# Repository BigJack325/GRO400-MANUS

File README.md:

# GRO400-MANUS
4th Semester Upgraded Hexapod Project for Robotique Engineering Sherbrooke University

<div id="ManUS" align="center">
    <h1>ManUS</h1>
    <h3>Hexapod Robot : Upgraded Version | Promo66-UdeS-GRO</h3>
</div>
<div id="badges" align="center">

</div>

**This academic project is based on an older academic project from robotic engineering undergraduates at Université de Sherbrooke. "Manu" is an hexapod robot able to interact with his environments. Along with 6 legs comes a camera mounted on a 3D printed head, elevating Manu to a whole new level of robotic hexapod. It can walk, look around and chase targets all around him in a restrained area/arena.**

## Table of Contents
- [Setup](#Setup)
    - [Setup for Users](#SetupUsers)
- [Documentation](#Documentation)
    - [Servos Classification](#Servosclassification)
    - [Assembly Guide](#assemblyguide)
    - [Electrical Schematic](#electricalschematic)
    - [Electrical Diagram of the Shield](#electrical)
    - [Code Overview](#Codeexplication)
- [Robot Operation](#Operation)
    - [Robot Movement](#Movement)
    - [Robot Vision](#Vision)
    - [HMI And Robot Controls](#Controls)
- [External Resources](#Ressources)
    - [Battery, Power Source, and Charger](#Battery)
    - [Microcontroller Board](#Controller)
    - [On-Board Computer](#Computer)
    - [Servomotor for the legs](#Servo1)
    - [Servomotor for the mandibles](#Servo2)
    - [Current Sensor](#Current)
    - [DC/DC Converter](#DCDC)
    - [Fuse 10 Amp](#Fuse)

## Setup

#### Setup for Users

<b>Step 1.</b> Connect Raspberry Pi camera to the Raspberry Pi before booting it up;
<br/>
<b>Step 2.</b> Clone this repository: https://github.com/EDP325/GRO400-MANUS.git
<br/>
<b>Step 3.</b> Create a new virtual environment, install dependencies, and add virtual environment to the Python Kernel by running in terminal:
<pre>
cd ./Hexapod-Master/Hexapod_Qt
./install_venv_pi.sh
</pre> 
<b>Step 4.</b> Connect the hexapod's microcontroller (Arduino) to Raspberry Pi;
<br/>
<b>Step 5.</b> Open the file <b>main.cpp</b> in the <b>./Hexapod-Master/Hexapod_Arduino/src</b> folder, and build the code into the microcontroller with your favorite IDE with PlatformIO;
<br/>
<b>Step 6.</b> Upload the <b>main.cpp</b> in the Arduino;
<br/>
<b>Step 7.</b> Run the file <b>MANUS_QT</b> in the <b>./Hexapod-Master/Hexapod_Qt</b> folder;
<br/>
<b>Step 8.</b> Initialize the serial communication.

## Documentation
#### <a id = "Servosclassification">Classification of the robot servos:</a>

#### <a id= "assemblyguide">Assembly Guide</a>
You need to 3D print the necessary parts that you can find in the *./CAD* folder.   
We have a complete assembly guide [here](https://github.com/EDP325/GRO400-MANUS/wiki):

#### <a id = "electricalschematic"> Electrical Schematic</a>

#### <a id= "electrical">Electrical Diagram of the Shield: </a>

#### <a id="Codeexplication">Code Overview</a>

The code is divided in two main sections. The first one is all about the robot's movment and is written in C++ and is run on the Arduino.  This code uses switch cases depending one the manuel/automatic mode and which movment to do.
The second section  includes the vision algorithm and the HMI.  It is written in Python and is run on the Raspberry Pi.  It is made to detect the chosen images and display  the HMI, a screen connected to the Pi.  We chose to use VNCviewer to connect to the Raspberry Pi through Wifi to have a remote connection to the hexapod.

## Robot Operation

#### Robot Movement
The robot can move forward, backward and sideways.  It can also rotate clockwise and counterclockwise.  The head can rotate and the mandibles can open cand close.  

#### Robot Vision
The robot has a vision algorithm that detects these two images: 

#### HMI And Robot Controls
Our HMI shows:
- The current view of the cam with TensorFlow AI detection;
- The angles of all the servos;
- A map of the arena with the position of the hexapod;
- Informations for the camera and messages from the Arduino
- Information about battery voltage percentage
- A graphic that shows the the value of a variable over time
- A ComboBox to see every connected ports to initialize serial communication
- Buttons to move the robots

## External ressources

Under this section, you will find external links and descriptions of the project's external resources.

#### Battery

- Brand Name: Makita
- Model:
    - Battery: BL1041B
    - Power Source: PE00000028
    - Charger: DC10SB
- ASIN:
    - Battery: B017GQJDVM
    - Charger: B01FY4XCB0
- Information / Resources:
    - [Makita Battery Webpage](https://www.makitatools.com/products/details/BL1041B)
    - [Makita Power Source Webpage](https://www.makitatools.com/products/details/PE00000028)
    - [Makita Charger Webpage](https://www.makitatools.com/products/details/DC10SB)

#### Microcontroller board

- Brand Name: Arduino
- Model: Mega 2560 R3 (A000067)
- ASIN: B0046AMGW0
- Information / Resources: [Arduino Webpage](https://store.arduino.cc/mega-2560-r3)

#### Onboard computer

- Brand Name: Raspberry Pi
- Model: 3B
- ASIN: B01LPLPBS8
- Information / Resources: [Raspberry Pi Webpage](https://www.raspberrypi.org/products/raspberry-pi-3-model-b/)

#### Servomotor for the legs

- Brand Name : VIPMOON
- Model : MG996R
- Information / Resources : [Amazon Webpage](https://www.amazon.ca/-/fr/gp/product/B07VT5T9JC/ref=ewc_pr_img_1?smid=A2FI4MJY3VQVX5&psc=1)

#### Servomotor for the mandibles

- Model : MG90S
- Information / Resources : [Amazon Webpage](https://www.amazon.ca/servomoteur-h%C3%A9licopt%C3%A8re-m%C3%A9tallique-intelligent-commandes/dp/B08W26FNQD/)
#### Current sensor

- Brand Name : ROBOJAX
- Model : ACS712
- ASIN :B07YP4693C
- Information / Resources : [Amazon Webpage](https://www.amazon.ca/gp/product/B07YP4693C/ref=ppx_yo_dt_b_asin_title_o02_s00?ie=UTF8&psc=1)

#### DC/DC Converter

- Brand Name : Tyenaza
- Model : Tyenazad03xwg94zo
- ASIN :
- Information / Resources : [Amazon Webpage](https://www.amazon.ca/gp/product/B097QT54C7/ref=ppx_yo_dt_b_asin_title_o02_s00?ie=UTF8&amp&psc=1)

#### Pi Camera

- Brand Name : Keyestudio
- Model : 8541582798
- ASIN :
- Information / Resources : [Amazon Webpage](https://www.amazon.ca/gp/product/B073RCXGQS/ref=ppx_yo_dt_b_asin_title_o01_s00?ie=UTF8&psc=1)
    
fuse 10 AMP
#### <a id="Fuse">Fuse 10 AMP 250V</a>

- Brand Name : Littelfuse
- Model : Littelfuse 5x15MM. FAST ACTING 10A.250V.
- Information / Resources :You can buy fuse at any electronics store near your house.  We bought ours [here](https://electro5.com/fr/product/231621/littlefuse-5x15mm-fast-acting-10a250v/)

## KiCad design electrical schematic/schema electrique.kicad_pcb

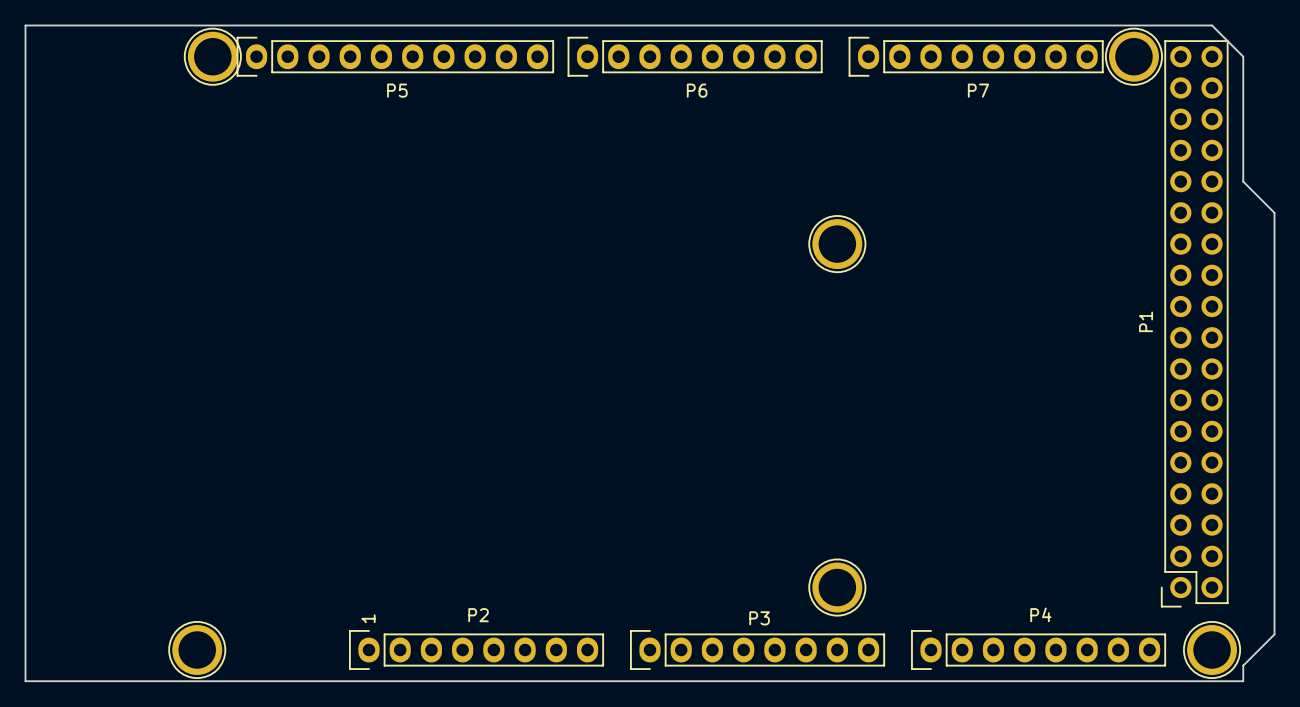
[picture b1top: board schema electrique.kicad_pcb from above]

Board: 2 copper layers, 101.6 x 53.3 mm, 13 parts (0 on the bottom side), 2 nets, no tracks yet.

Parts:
P1: Digital; Socket_Strip_Arduino_2x18
P2: Power; Socket_Strip_Arduino_1x08
P3, P4: Analog; Socket_Strip_Arduino_1x08
P5: PWM; Socket_Strip_Arduino_1x10
P6: PWM; Socket_Strip_Arduino_1x08
P7: Communication; Socket_Strip_Arduino_1x08
P8, P9, P10, P11, P12, P13: CONN_01X01; Arduino_1pin

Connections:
+5V: P1.35, P1.36, P2.5
GND: P1.1, P1.2, P2.6, P2.7, P5.4

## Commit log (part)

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2022-03-09 Virtual environement
2022-03-09 Code Max main Arduino
2022-03-14 TensorFlow Update
2022-03-19 Libraries Update
2022-03-19 Library Update
2022-03-19 Installation update
2022-03-22 Tensorflow sur HMI
2022-03-23 Images_Camera_Pi
2022-03-28 Update serialCom et Jupyter pour prendre photo
2022-03-28 tflite upgrade
2022-03-28 gitignore change
2022-03-28 Sequence mouvement
2022-03-28 Update Pat Jupyter
2022-03-28 update des librairies megaservo
2022-03-28 Message JSON Brower réduit
2022-03-29 More photos
2022-03-29 Correction des cases
2022-03-29 allo
2022-03-29 Update Com
2022-03-30 fonction current sensor
2022-03-30 bon current
2022-03-30 Distance Camera
2022-04-06 pin mode ajouté
2022-04-06 Smooth Movement
2022-04-06 New Images
2022-04-06 offset servos
2022-04-06 pat gras
2022-04-06 Initial angle setting
2022-04-06 mode automatic semi completer
2022-04-08 Update Bouton
2022-04-08 Prevent movement when down
2022-04-08 Button HMI
2022-04-08 correction dune condition if
2022-04-09 Correction de la condition electrical shutdown
2022-04-09 Ajout des case turn head
2022-04-09 push to pull
2022-04-09 photo label
2022-04-09 Nouvelles images proche
2022-04-09 Update gitignore
2022-04-11 Update Vision Com et Bouttons
2022-04-11 2nd part automatic
2022-04-12 Create image
2022-04-12 Position avec avancer
2022-04-12 Retirer test_variable
2022-04-12 Ajouter variable importante
2022-04-12 Implementer change in orientation
2022-04-12 Update com et vision
2022-04-12 ajout mode auto
2022-04-12 DEEZ NUTZ
2022-04-13 Conversion pour pixel map
2022-04-13 Map_Update
2022-04-13 correction mapping + backward
2022-04-13 mapping edit
2022-04-13 Update_Map
2022-04-13 Update_repo
2022-04-13 mapping correction
2022-04-13 automatic min distance detect
2022-04-13 ajout de definition de variable
2022-04-13 correction de limit tourner et garde detection en memoir
2022-04-13 Bruh
2022-04-13 Ajout de mapping pour side step
2022-04-13 Update_Com
2022-04-13 fonction futureposition et update position
2022-04-13 retry
2022-04-13 change turn head format
2022-04-13 Update_head
2022-04-13 fix mandibules
2022-04-13 merge
2022-04-14 code derniere journe
2022-04-14 Code Semi-final
2022-04-14 correction automatic
2022-04-14 Final
2022-04-15 Create LICENSE
2022-04-15 Create Dockerfile
2022-04-15 Create Makefile
2022-04-15 Update Dockerfile
2022-04-16 Update fin
2022-04-16 Big Update
2022-04-16 venv update
2022-04-16 update more
2022-04-16 More update
2022-04-16 test
2022-04-16 last try
2022-04-16 Update tensorflow
2022-04-16 Update TF
2022-04-16 tests
2022-04-17 platform test
2022-04-17 plateformio action
2022-04-17 Qt docker test
2022-04-17 Arduino test
2022-04-18 Qt CI

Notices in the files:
README.md:
License: GPL v3
